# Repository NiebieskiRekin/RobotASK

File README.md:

# Robot ASK - Piano tiles

A Piano Tiles (mobile game) hardware autoclicker built on the ATmega328. All electrical sketches and the PCB were designed in [KiCad](https://www.kicad.org/). Code for the microprocessor was written in C++ using Arduino and Servo libraries as well as the [PlatformIO](https://platformio.org/install/ide?install=vscode) VSCode extension.

This project also has a live visualisation Python script that communicates with the main board over serial to display data captured by the photoresistor module. This script can also be used to quickly adjust some parameters at the start of runtime.

This repository was created for a university group project for [RoboDay 2024](https://www.facebook.com/events/1518830758974874) at Poznań University of Technology.
Made by: Tomasz Pawłowski, Jakub Kamieniarz, Jakub Buler, Adam Deter

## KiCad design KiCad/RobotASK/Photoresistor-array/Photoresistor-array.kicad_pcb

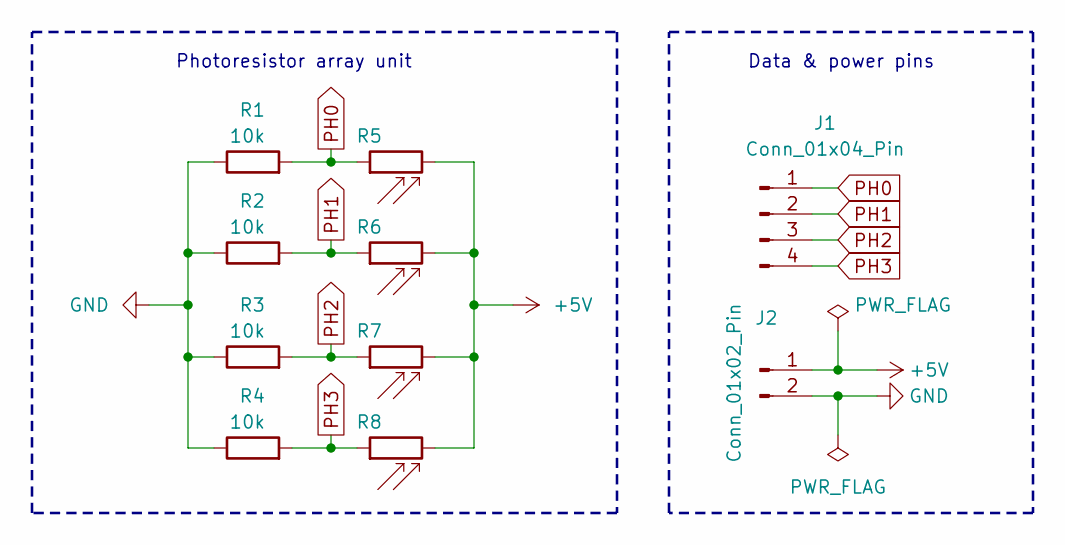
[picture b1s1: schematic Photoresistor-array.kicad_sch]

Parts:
J1: Conn_01x04_Pin; PinHeader_1x04_P2.54mm_Vertical
J2: Conn_01x02_Pin; PinHeader_1x02_P2.54mm_Vertical
R1, R2, R3, R4: 10k; R_Axial_DIN0207_L6.3mm_D2.5mm_P10.16mm_Horizontal
R5, R6, R7, R8: 5-10k; R_LDR_5.1x4.3mm_P3.4mm_Vertical

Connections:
+5V: J2.1, R5.2, R6.2, R7.2, R8.2
GND: J2.2, R1.1, R2.1, R3.1, R4.1
PH0: J1.1, R1.2, R5.1
PH1: J1.2, R2.2, R6.1
PH2: J1.3, R3.2, R7.1
PH3: J1.4, R4.2, R8.1

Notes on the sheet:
Data & power pins
Photoresistor array unit

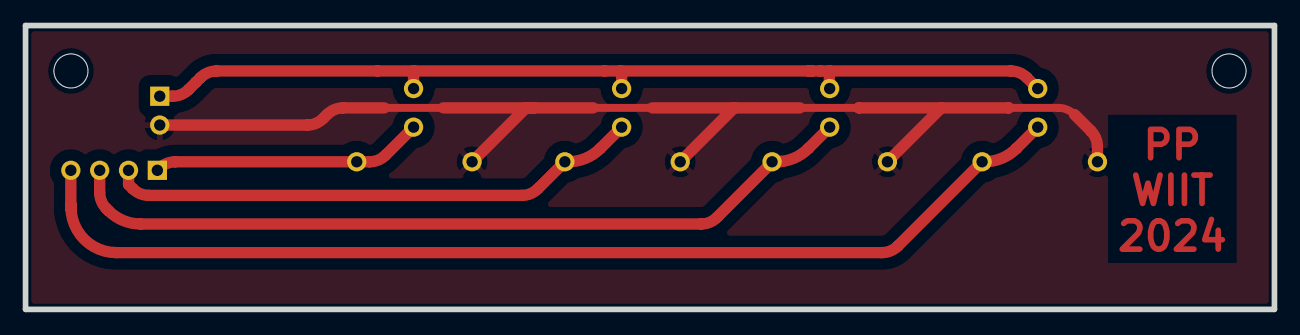
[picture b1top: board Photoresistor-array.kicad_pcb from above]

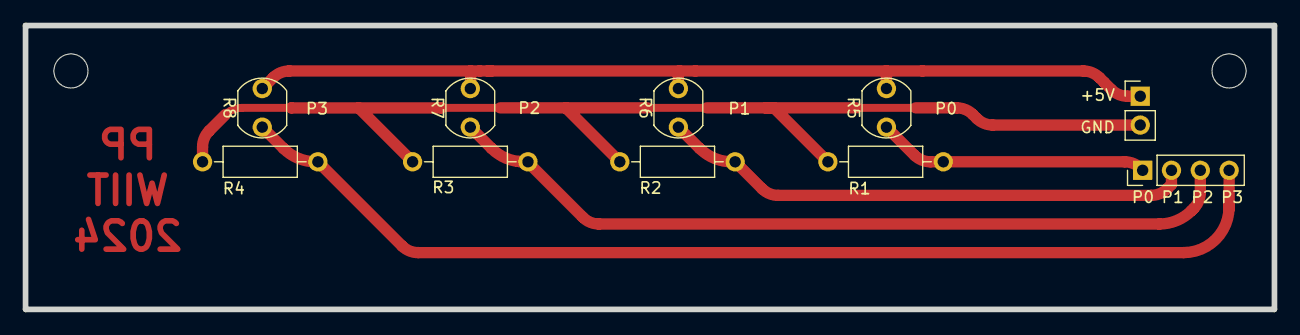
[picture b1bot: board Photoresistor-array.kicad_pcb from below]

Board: 2 copper layers, 110.0 x 25.0 mm, 10 parts (10 on the bottom side), 6 nets.

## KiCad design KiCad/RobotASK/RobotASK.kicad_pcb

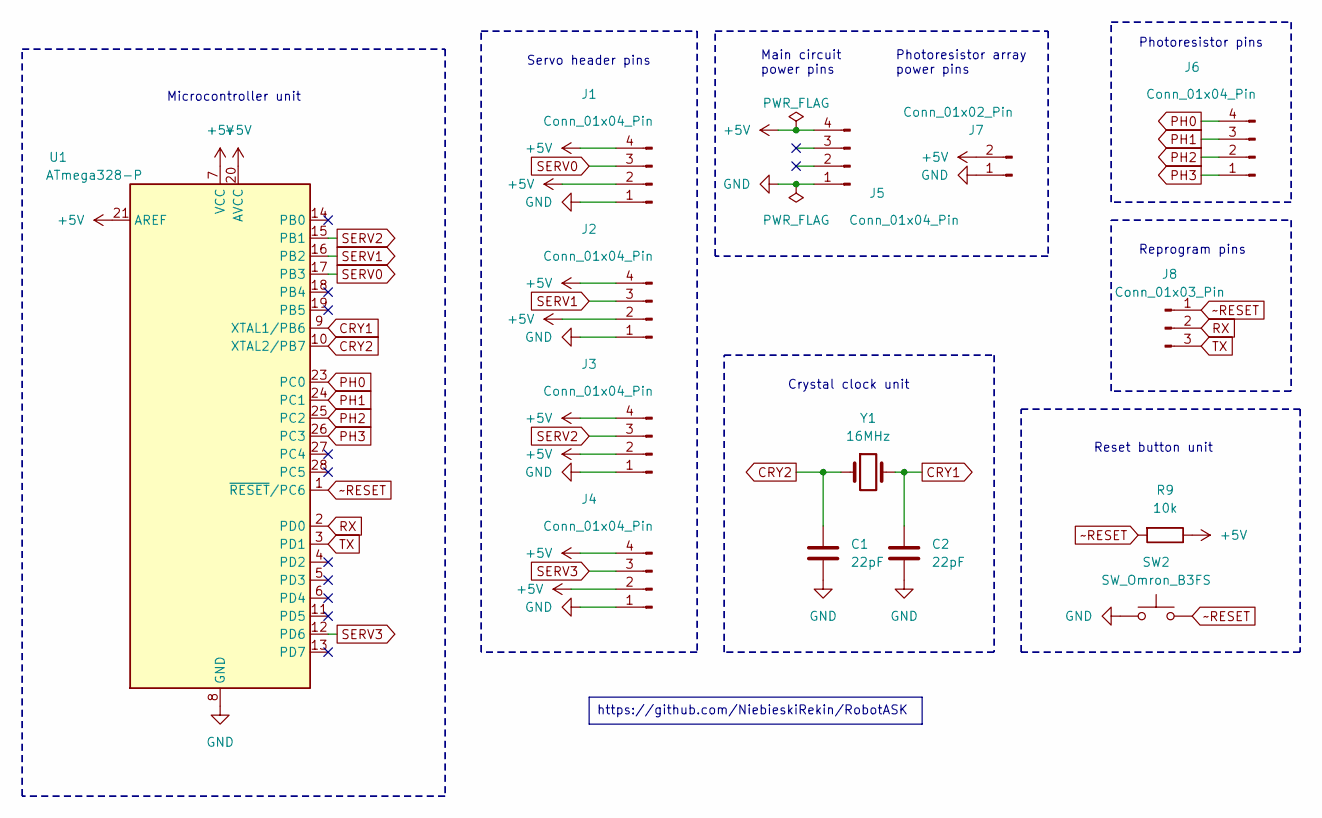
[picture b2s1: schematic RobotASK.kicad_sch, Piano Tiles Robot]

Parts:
C1, C2: 22pF; C_Disc_D3.8mm_W2.6mm_P2.50mm
J1, J2, J3, J4, J6: Conn_01x04_Pin; PinHeader_1x04_P2.54mm_Vertical
J5: Conn_01x04_Pin; USB-C Socket Breakout Board
J7: Conn_01x02_Pin; PinHeader_1x02_P2.54mm_Vertical
J8: Conn_01x03_Pin; PinHeader_1x03_P2.54mm_Vertical
R9: 10k; R_Axial_DIN0207_L6.3mm_D2.5mm_P10.16mm_Horizontal
SW2: SW_Omron_B3FS; SW_PUSH_6mm_H4.3mm
U1: ATmega328-P; DIP-28_W7.62mm
Y1: 16MHz; Crystal_HC49-4H_Vertical

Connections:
+5V: J1.2, J1.4, J2.2, J2.4, J3.2, J3.4, J4.2, J4.4, J5.4, J7.2, R9.1, U1.7 (VCC), U1.20 (AVCC), U1.21 (AREF)
CRY1: C2.1, U1.9 (XTAL1/PB6), Y1.2
CRY2: C1.1, U1.10 (XTAL2/PB7), Y1.1
GND: C1.2, C2.2, J1.1, J2.1, J3.1, J4.1, J5.1, J7.1, SW2.1, U1.8 (GND), U1.22 (GND)
PH0: J6.4, U1.23 (PC0)
PH1: J6.3, U1.24 (PC1)
PH2: J6.2, U1.25 (PC2)
PH3: J6.1, U1.26 (PC3)
RX: J8.2, U1.2 (PD0)
SERV0: J1.3, U1.17 (PB3)
SERV1: J2.3, U1.16 (PB2)
SERV2: J3.3, U1.15 (PB1)
SERV3: J4.3, U1.12 (PD6)
TX: J8.3, U1.3 (PD1)
~RESET: J8.1, R9.2, SW2.2, U1.1 (~RESET/PC6)

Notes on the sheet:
https://github.com/NiebieskiRekin/RobotASK
Photoresistor pins
Microcontroller unit
Reprogram pins
Crystal clock unit
Reset button unit
Main circuit power pins
Photoresistor array power pins
Servo header pins

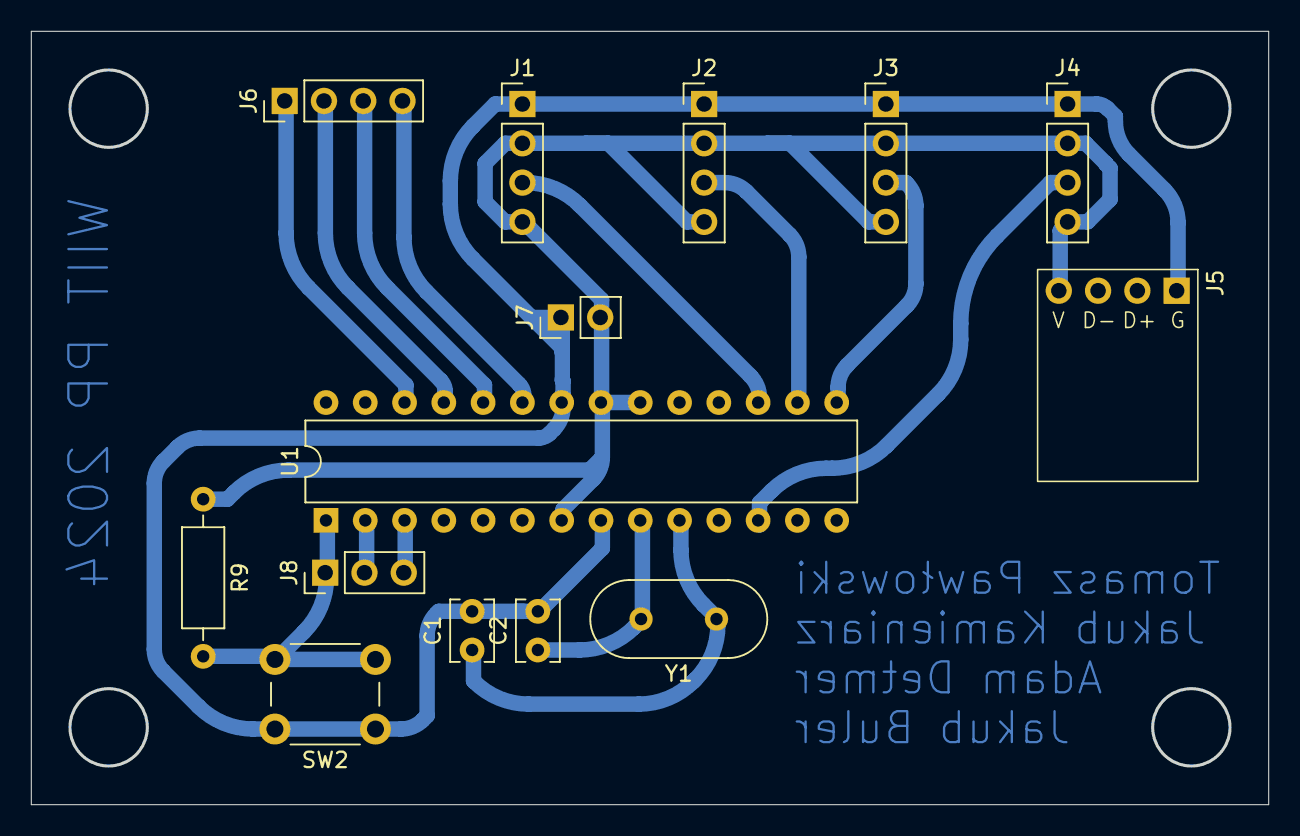
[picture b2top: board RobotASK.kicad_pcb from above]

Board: 2 copper layers, 79.9 x 49.9 mm, 14 parts (0 on the bottom side), 15 nets.

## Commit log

2024-03-07 pomysły na robota
2024-03-09 Init
2024-03-19 Piano tiles na jedną płytkę
2024-03-19 Podstawowy na 4 servo
2024-04-02 PCB całego układu + rendery
2024-04-03 reprogrammable pins
2024-04-03 step export
2024-04-03 Bez zbędnego pinu GND, update KiCad 8, export ze ścieżkami
2024-04-04 Lista rzeczy do PCB
2024-04-07 Wymiary PCB
2024-04-07 Poprawka wartstw + wydruki
2024-04-07 przycięcie do zawartości
2024-04-08 Płytka fotorezystorów przedłużona aby piny były na dole
2024-04-08 Aktualizacja wymiarów
2024-04-09 procedura UV pcb
2024-04-09 update servo pins
2024-04-14 Podsumowanie trawienia płytki
2024-04-14 Kod do programu z monetami
2024-04-14 Kicad backups
2024-04-14 literówki
2024-04-14 Poszerzenie wszystkich możliwych ścieżek, wypełnienie edge cuts, poszerzenie płytki z fotorezystorami o 2mm
2024-04-28 Poprawki kodu, zwiększenie otworów na komponenty na 1mm, nowe wydruki do termotransferu i nawiercania otworów, poukładanie nieaktualnych wydruków UV
2024-04-29 Kod który nabił 450
2024-05-03 Zmiana parametrów poprzez Serial, dużo ładniejszy interfejs serial
2024-05-03 Update Baud rate
2024-05-03 Updated config file
2024-05-03 Update upload port
2024-05-03 Better config
2024-05-03 input format serial
2024-05-04 Przeniesienie do docs
2024-05-04 update config
2024-05-05 Sterowanie ze skryptu wyświetlającego dane w matplot
2024-05-06 ladniejsze wyswietlanie
2024-05-06 OpenCV rewrite
2024-05-07 simple scrolling and code formatting
2024-05-07 Działa w porządku, tylko trochę jitter przez przeskakiwanie po pikselach
2024-05-07 update TODO
2024-05-07 pretty print w terminalu ze skryptu
2024-05-08 kod na 1626 na level 8. Bluestone Alley
2024-05-08 Zaktualizuj defaultowe kąty
2024-05-08 Odbicie obrazu aby kafelki szły od góry
2024-05-08 Render
2024-05-08 renders
2024-05-09 Ideas for the project
2024-05-09 Add PlatformIO project template
2024-05-09 Add code to detect and click a single tile
2024-05-09 Extend code to four parallel tiles
2024-05-09 Schematic and PCB
2024-05-09 PCB renders (images and 3D models)
2024-05-09 Main pcb .step export
2024-05-09 Add pins to quickly reprogram the microprocessor
2024-05-09 Remove redundant GND pin & migrate to KiCad8
2024-05-09 Add .step 3D exports with traces
2024-05-09 Add manual PCB etching checklist
2024-05-09 Edit pcb layers
2024-05-09 Update 3D .step exports
2024-05-09 Add gerber files and prints for manual etching
2024-05-09 Add a bill of materials needed for PCB etching
2024-05-09 Make photoresistor PCB single layer
    The printed circuit board of the photoresitor array submodule was
    increased in length to accomodate the power and signal goldpins on the
    same side as the resistors and photoresistors. This allows us to make
    a single layer PCB, which is much easier handmade.
2024-05-09 Update manual PCB etching checklist
    Update ListaPCB.md
2024-05-09 Update servo pins & code formatting
2024-05-09 Add procedure for PCB etching using photosensitive film
2024-05-09 Add code that uses coins instead of servos
    Alternative version of the project that uses coins to which voltage is
    applied as a means to register touch press on a screen in order to
    replace somewhat complicated servo physical limitations.
2024-05-09 Widen all possible traces, fill edge cuts layer, widen photoresistor PCB by 2mm
2024-05-09 Increase the size of component holes and pads
2024-05-09 Code bug fix
2024-05-09 Add new PCB prints (toner etching & drilling), order old ones
    Added new prints exports of the PCB for the heat toner transfer method and drilling holes. Ordered old prints for the method using photosensitive film
2024-05-09 Save code version that reached a score of 452 points
2024-05-09 Refresh PCB backups
2024-05-09 Remove unused coins.cpp
2024-05-09 Add communication over serial port
    Added the option of changing program parameters at during the first 10s of runtime. Added a pretty print of the values read by the robot over serial. Baud rate set to 115200 bauds.
2024-05-09 Move old documents to /docs
2024-05-09 Prettify the PCB and create renders
2024-05-09 Add a script that visualises photoresistor reads
    Added a python script that displays an image that resembles the game
    screen based on the photoresitor measurements for each frame.
    Required dependencies: `pip install pyserial opencv-python numpy`
    The main code running on the ATmega328 was simplified, all of the
    terminal pretty printing was moved to the script. Debug serial output
    from the microprocessor is minimal.
2024-05-10 Update img exports
